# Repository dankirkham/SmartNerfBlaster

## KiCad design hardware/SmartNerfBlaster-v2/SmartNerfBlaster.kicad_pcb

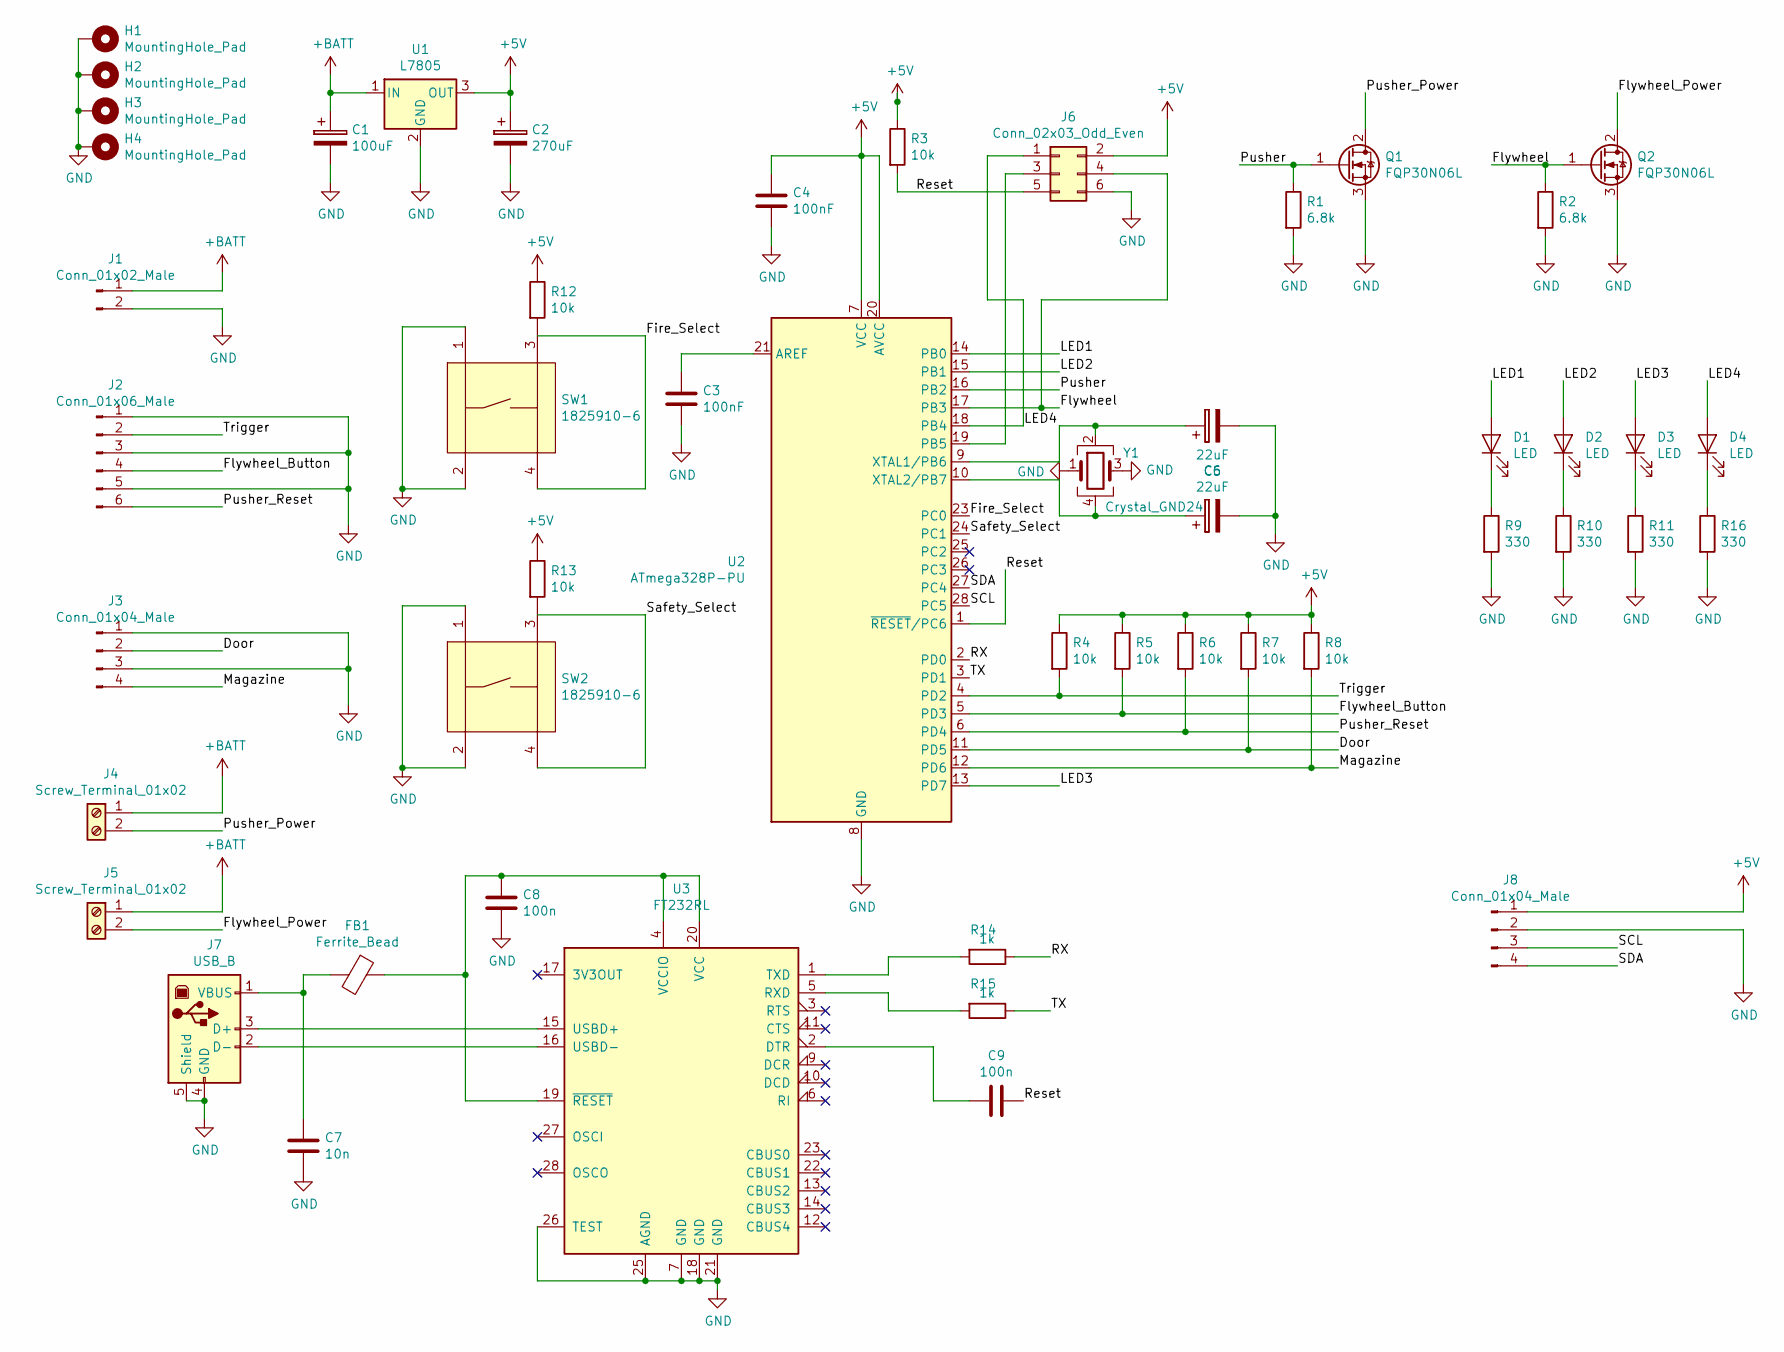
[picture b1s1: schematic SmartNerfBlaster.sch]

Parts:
C1: 100uF; CP_Radial_D5.0mm_P2.50mm
C2: 270uF; CP_Radial_D5.0mm_P2.50mm
C3, C4: 100nF; C_0603_HandSoldering
C5, C6: 22uF; C_0805_HandSoldering
C7: 10n; C_0805_HandSoldering
C8, C9: 100n; C_0603_HandSoldering
D1, D2, D3, D4: LED; LED_0805_HandSoldering
FB1: Ferrite_Bead; R_0805_HandSoldering
H1, H2, H3, H4: MountingHole_Pad; MountingHole_3.2mm_M3_Pad
J1: Conn_01x02_Male; PowerPads
J2: Conn_01x06_Male; JST_XH_B06B-XH-A_06x2.50mm_Straight
J3: Conn_01x04_Male; JST_XH_B04B-XH-A_04x2.50mm_Straight
J4, J5: Screw_Terminal_01x02; PowerPads
J6: Conn_02x03_Odd_Even; Pin_Header_Straight_2x03_Pitch2.54mm
J7: USB_B; USB_Mini-B
J8: Conn_01x04_Male; Pin_Header_Straight_1x04_Pitch2.54mm
Q1, Q2: FQP30N06L; TO-220-3_Vertical
R1, R2: 6.8k; R_0603_HandSoldering
R3, R4, R5, R6, R7, R8, R12, R13: 10k; R_0603_HandSoldering
R9, R10, R11, R16: 330; R_0603_HandSoldering
R14, R15: 1k; R_0603_HandSoldering
SW1, SW2: 1825910-6
U1: L7805; TO-220-3_Vertical
U2: ATmega328P-PU; TQFP-32_7x7mm_Pitch0.8mm
U3: FT232RL; SSOP-28_5.3x10.2mm_P0.65mm
Y1: Crystal_GND24; Crystal_SMD_3225-4pin_3.2x2.5mm_HandSoldering

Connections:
+5V: C2.1, C4.1, J6.2, J8.1, R3.1, R4.1, R5.1, R6.1, R7.1, R8.1, R12.1, R13.1, U1.3 (OUT), U2.7 (VCC), U2.20 (AVCC)
+BATT: C1.1, J1.1, J4.1, J5.1, U1.1 (IN)
/Door: J3.2, R7.2, U2.11 (PD5)
/Fire_Select: SW1.4, U2.23 (PC0)
/Flywheel: J6.4, Q2.1 (G), R2.1, U2.17 (PB3)
/Flywheel_Button: J2.4, R5.2, U2.5 (PD3)
/Flywheel_Power: J5.2, Q2.2 (D)
/LED1: D1.2 (A), U2.14 (PB0)
/LED2: D2.2 (A), U2.15 (PB1)
/LED3: D3.2 (A), U2.13 (PD7)
/LED4: D4.2 (A), J6.1, U2.18 (PB4)
/Magazine: J3.4, R8.2, U2.12 (PD6)
/Pusher: Q1.1 (G), R1.1, U2.16 (PB2)
/Pusher_Power: J4.2, Q1.2 (D)
/Pusher_Reset: J2.6, R6.2, U2.6 (PD4)
/RX: R14.1, U2.2 (PD0)
/Reset: C9.1, J6.5, R3.2, U2.1 (~RESET~/PC6)
/SCL: J8.3, U2.28 (PC5)
/SDA: J8.4, U2.27 (PC4)
/Safety_Select: SW2.4, U2.24 (PC1)
/TX: R15.1, U2.3 (PD1)
/Trigger: J2.2, R4.2, U2.4 (PD2)
GND: C1.2, C2.2, C3.2, C4.2, C5.2, C6.2, C7.2, C8.2, H1.1, H2.1, H3.1, H4.1, J1.2, J2.1, J2.3, J2.5, J3.1, J3.3, J6.6, J7.4 (GND), J7.5 (Shield), J8.2, Q1.3 (S), Q2.3 (S), R1.2, R2.2, R9.2, R10.2, R11.2, R16.2, SW1.1, SW1.2, SW2.1, SW2.2, U1.2 (GND), U2.8 (GND), U2.22 (GND), U3.7 (GND), U3.18 (GND), U3.21 (GND), U3.25 (AGND), U3.26 (TEST), Y1.1, Y1.3
unnamed: C3.1, U2.21 (AREF)
unnamed: C5.1, U2.9 (XTAL1/PB6), Y1.2
unnamed: C6.1, U2.10 (XTAL2/PB7), Y1.4
unnamed: C7.1, FB1.2, J7.1 (VBUS)
unnamed: C8.1, FB1.1, U3.4 (VCCIO), U3.19 (~RESET~), U3.20 (VCC)
unnamed: C9.2, U3.2 (DTR)
unnamed: D1.1 (K), R9.1
unnamed: D2.1 (K), R10.1
unnamed: D3.1 (K), R11.1
unnamed: D4.1 (K), R16.1
unnamed: J6.3, U2.19 (PB5)
unnamed: J7.2 (D-), U3.16 (USBD-)
unnamed: J7.3 (D+), U3.15 (USBD+)
unnamed: R12.2, SW1.3
unnamed: R13.2, SW2.3
unnamed: R14.2, U3.1 (TXD)
unnamed: R15.2, U3.5 (RXD)

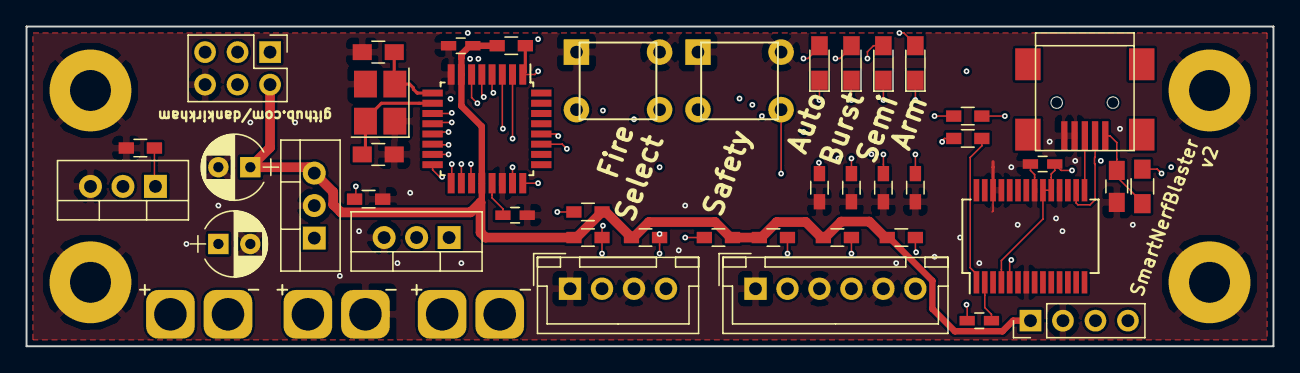
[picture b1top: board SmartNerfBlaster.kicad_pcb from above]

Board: 4 copper layers, 97.5 x 25.0 mm, 50 parts (0 on the bottom side), 40 nets.

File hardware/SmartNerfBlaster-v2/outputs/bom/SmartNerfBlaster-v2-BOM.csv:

"Designator","Package","Quantity","Designation","LCSC Part #"
"C3,C4","0603",2,"100nF","C14663",
"C5,C6","0805",2,"22uF","C45783",
"D1,D2,D3","LED_0805",3,"LED","C2297",
"D4","LED_0805",1,"LED","C84256",
"R1,R2","0603",2,"6.8k","C23212",
"R3,R4,R5,R6,R7,R8,R12,R13","0603",8,"10k","C25804",
"R9,R10,R11,R16","0603",4,"330","C23138",
"U2","TQFP-32_7.0x7.0x0.8P",1,"ATmega328P-PU","C14877",
"C7","0805",1,"10n","C1710",
"C8,C9","0603",2,"100n","C14663",
"FB1","0805",1,"Ferrite_Bead","C1017",
"R14,R15","0603",2,"1k","C21190",
"Y1","SMD-3225_4P",1,"Crystal_GND24","C13738",
"U3","SSOP-28_5.3x10.2x0.65P",1,"FT232RL","C8690",

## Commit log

2019-03-05 Added .gitignore.
2019-03-05 Add KiCad Project.
2019-03-05 Fixed libaray issues. Added gerbers and pdf outputs.
2019-03-05 Add README with known issues.
2019-03-05 Fixed more library issues.
2019-03-06 Added BOM.
2019-03-06 Add arduino sketch.
2019-03-06 Add assembly picture.
2019-03-06 Shrink assembly picture.
2019-03-09 Added select fire modes.
2019-03-10 Changed pusher reset switch logic for better burst fire modes. Adjusted PWM duty cycle for flywheel.
2020-07-13 Hardware v2.
